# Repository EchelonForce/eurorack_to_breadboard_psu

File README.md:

# Eurorack Bread Board Power Supply

This is a PCB for a bread board power supply for eurorack synthesizer development.

Full writeup here: https://www.robotdialogs.com/2022/08/breakout-boards-for-synthesizer.html

This work is licensed under a Creative Commons Attribution-NonCommercial-ShareAlike 4.0 International License. https://creativecommons.org/licenses/by-nc-sa/4.0/

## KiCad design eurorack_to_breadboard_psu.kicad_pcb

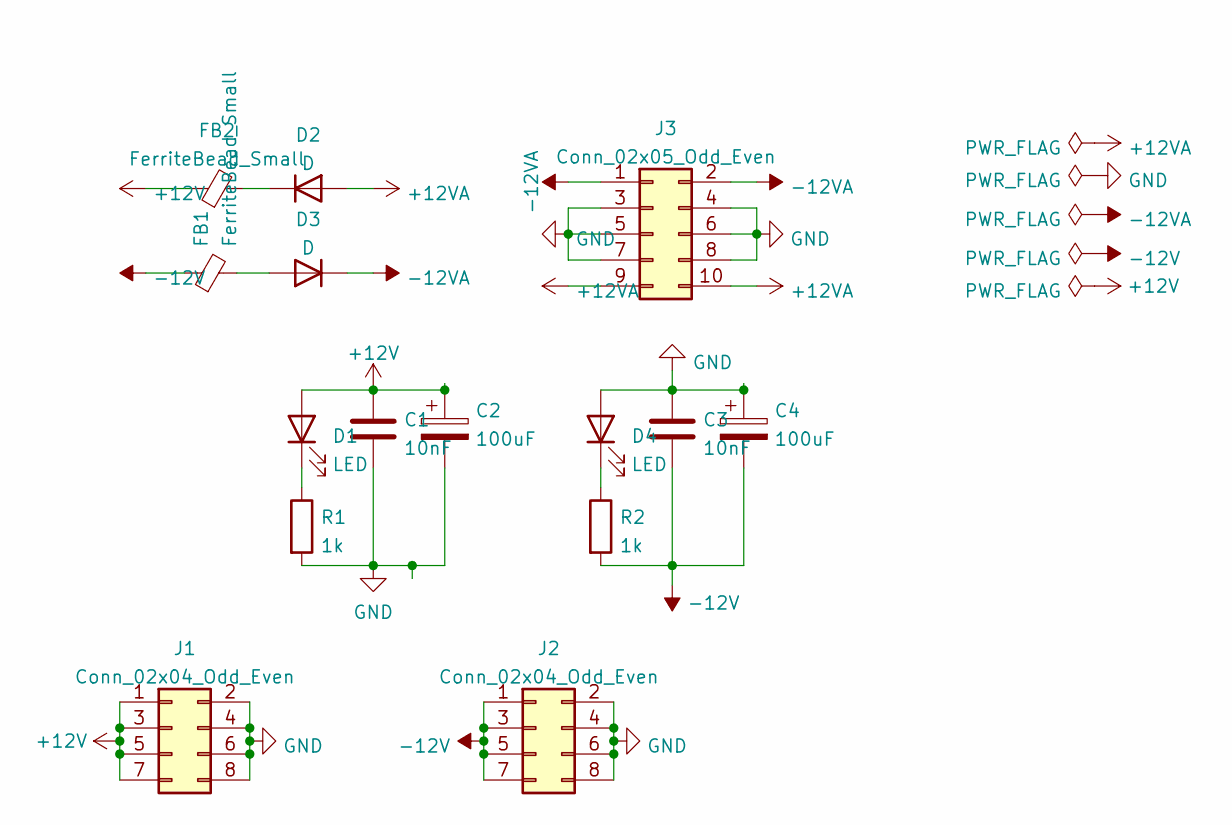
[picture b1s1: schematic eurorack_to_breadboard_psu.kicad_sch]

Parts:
C1, C3: 10nF; C_Disc_D5.1mm_W3.2mm_P5.00mm
C2, C4: 100uF; CP_Radial_D5.0mm_P2.50mm
D1, D4: LED; LED_D3.0mm
D2, D3: D; D_DO-15_P3.81mm_Vertical_KathodeUp
FB1, FB2: FerriteBead_Small; L_Axial_L9.5mm_D4.0mm_P5.08mm_Vertical_Fastron_SMCC
J1, J2: Conn_02x04_Odd_Even; PinHeader_2x04_P2.54mm_Vertical
J3: Conn_02x05_Odd_Even; IDC-Header_2x05_P2.54mm_Vertical
R1, R2: 1k; R_1206_3216Metric_Pad1.30x1.75mm_HandSolder

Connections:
+12V: C1.1, C2.1, D1.2 (A), FB2.1, J1.1, J1.3, J1.5, J1.7
+12VA: D2.2 (A), J3.9, J3.10
-12V: C3.2, C4.2, FB1.1, J2.1, J2.3, J2.5, J2.7, R2.2
-12VA: D3.1 (K), J3.1, J3.2
GND: C1.2, C2.2, C3.1, C4.1, D4.2 (A), J1.2, J1.4, J1.6, J1.8, J2.2, J2.4, J2.6, J2.8, J3.3, J3.4, J3.5, J3.6, J3.7, J3.8, R1.2
unnamed: D1.1 (K), R1.1
unnamed: D2.1 (K), FB2.2
unnamed: D3.2 (A), FB1.2
unnamed: D4.1 (K), R2.1

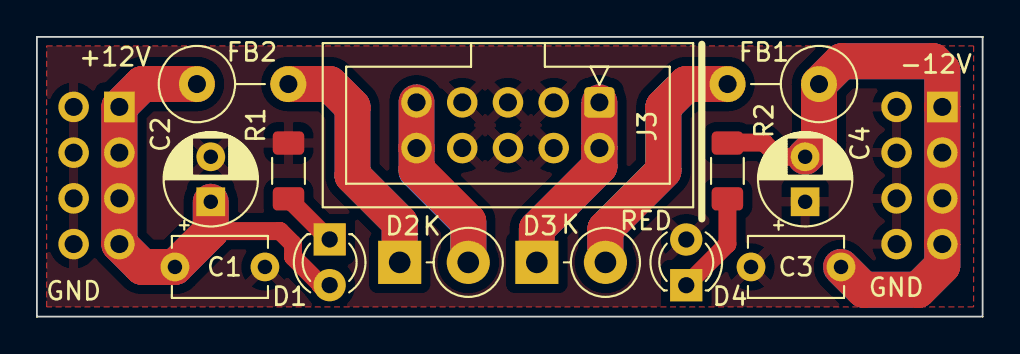
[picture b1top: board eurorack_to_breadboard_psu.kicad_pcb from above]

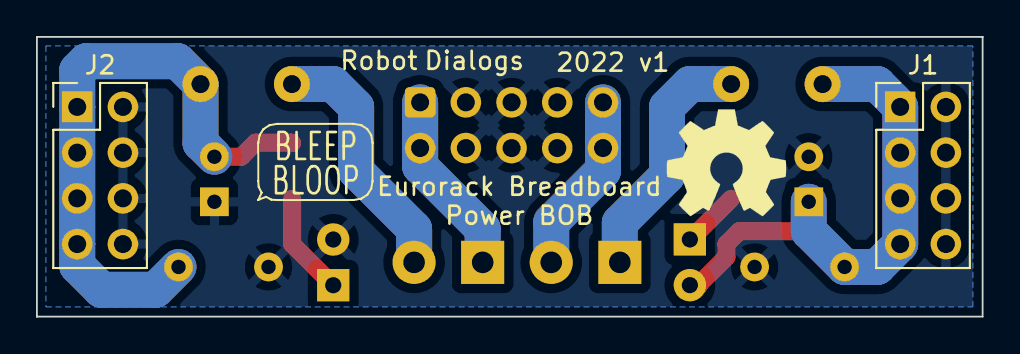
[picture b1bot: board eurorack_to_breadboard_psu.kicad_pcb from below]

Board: 2 copper layers, 52.5 x 15.5 mm, 15 parts (2 on the bottom side), 9 nets.

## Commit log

2022-02-19 Initial commit with .gitignore
2022-02-19 Version 1 PCB as ordered
2022-08-31 Notes on v1 boards
2022-08-31 Add readme
2022-08-31 Correct the readme
    Previous commit was just a copy paste error.
2022-08-31 Fix page labels and add schematic pdf
